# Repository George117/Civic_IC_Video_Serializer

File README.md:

# Civic_IC_Video_Serializer
Civic_IC_Video_Serializer

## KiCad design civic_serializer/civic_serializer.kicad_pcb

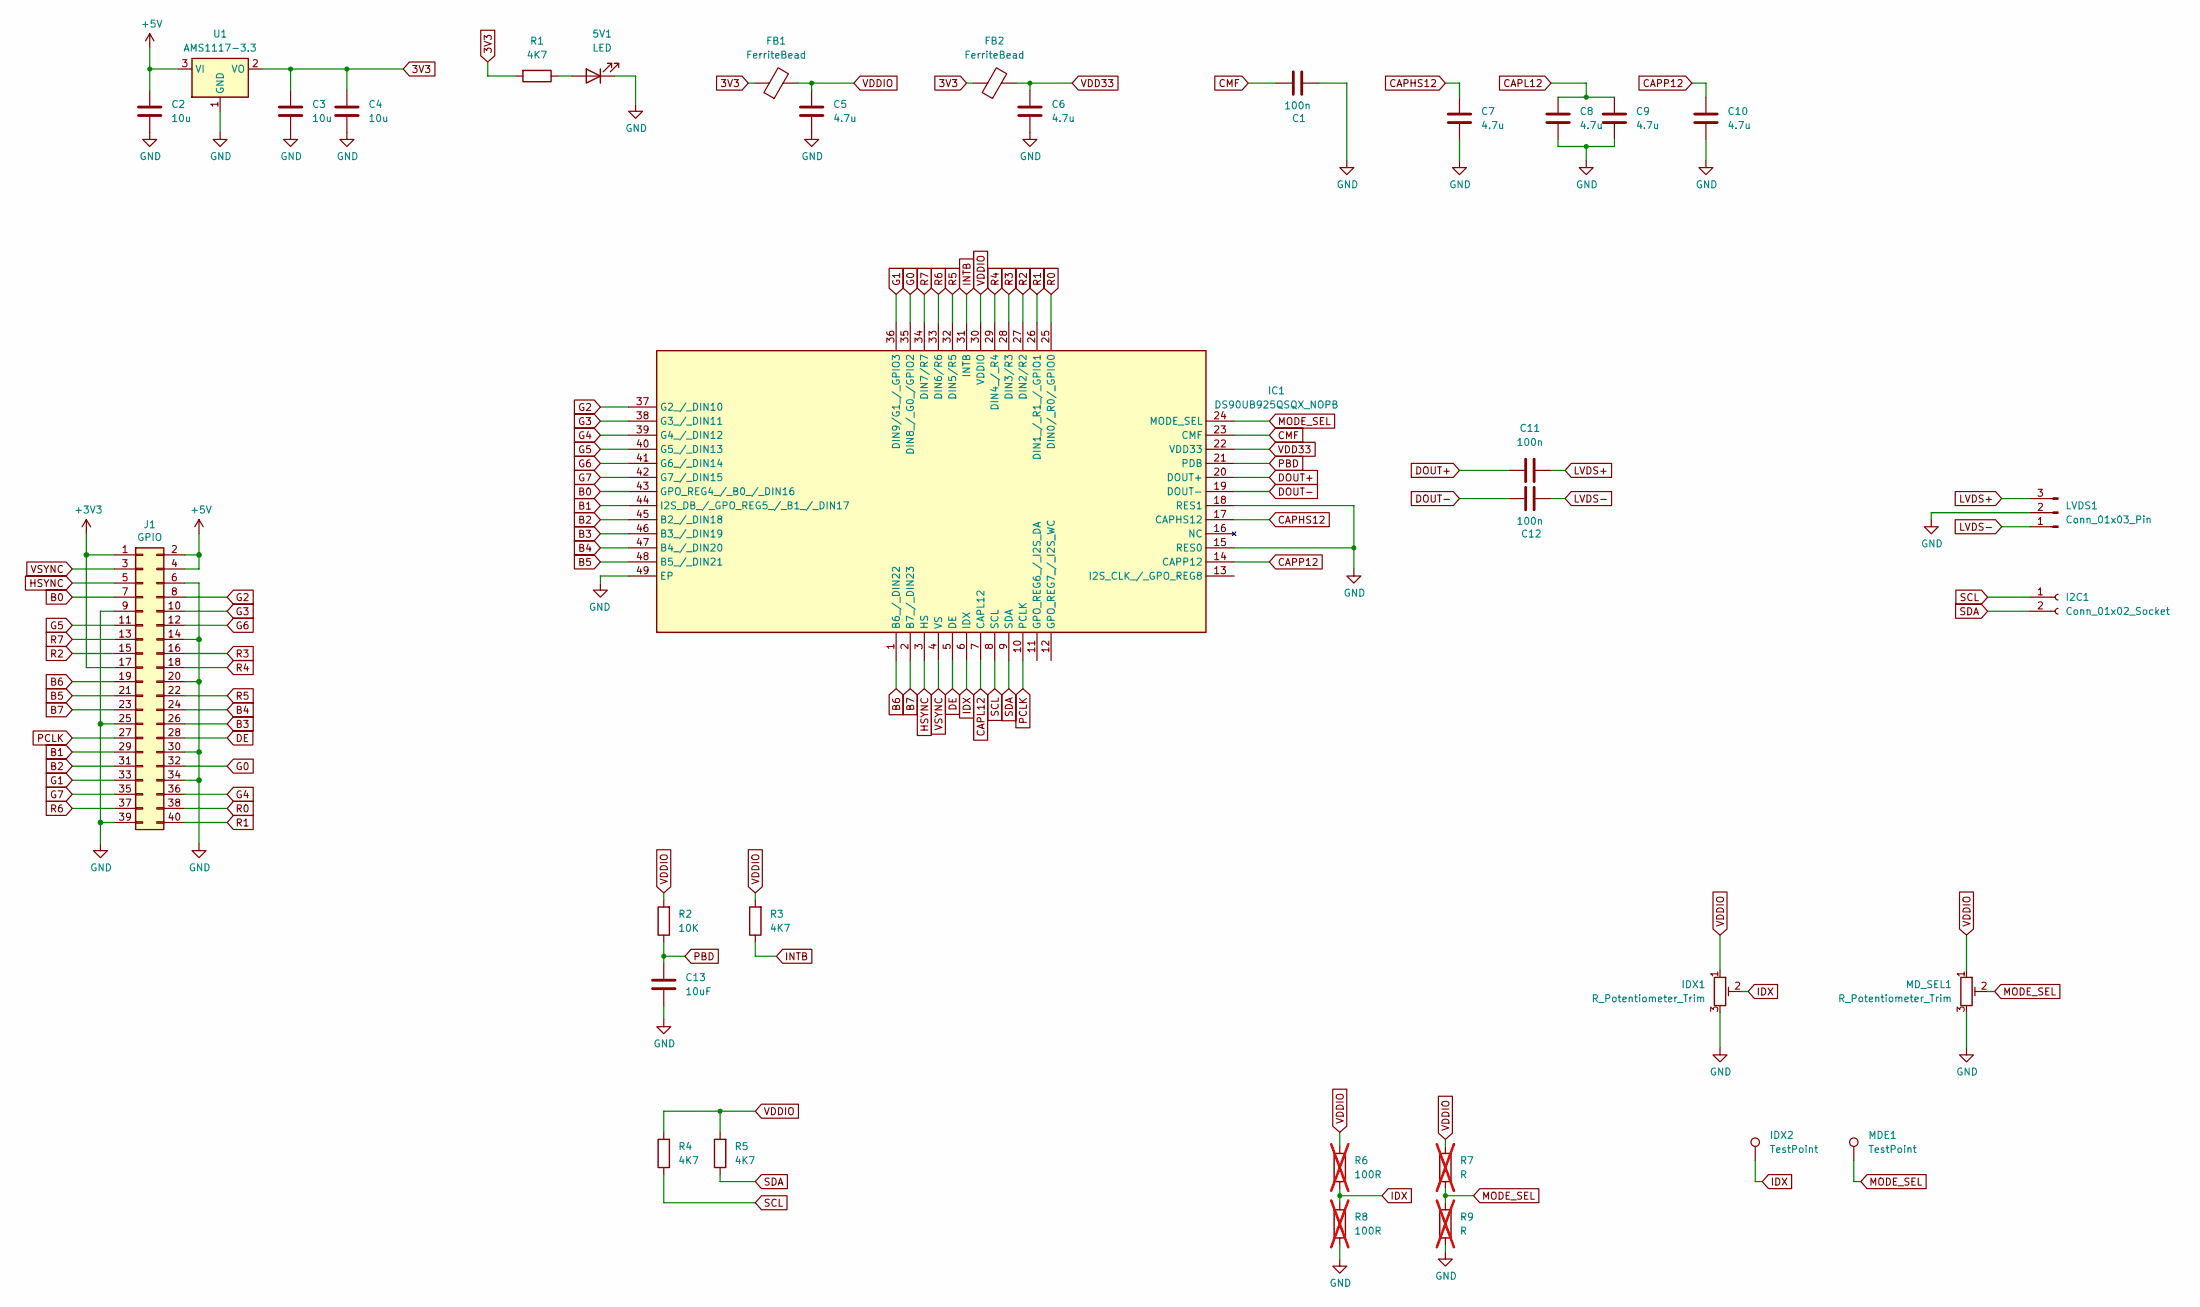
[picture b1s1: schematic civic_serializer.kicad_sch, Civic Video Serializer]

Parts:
5V1: LED; LED_0805_2012Metric_Pad1.15x1.40mm_HandSolder
C1, C11, C12: 100n; C_0603_1608Metric_Pad1.08x0.95mm_HandSolder
C2, C3, C4: 10u; C_0805_2012Metric_Pad1.18x1.45mm_HandSolder
C5, C6, C7, C8, C9, C10: 4.7u; C_0603_1608Metric_Pad1.08x0.95mm_HandSolder
C13: 10uF; C_0603_1608Metric_Pad1.08x0.95mm_HandSolder
FB1, FB2: FerriteBead; L_0603_1608Metric_Pad1.05x0.95mm_HandSolder
I2C1: Conn_01x02_Socket; PinSocket_1x02_P2.54mm_Vertical
IC1: DS90UB925QSQX_NOPB; QFN50P700X700X80-49N-D; Manufacturer_Part_Number DS90UB925QSQX/NOPB; Mouser Part Number 595-DS90UB925QSQXNPB
IDX1: R_Potentiometer_Trim; Potentiometer_Vishay_T93YA_Vertical
IDX2: TestPoint; PinSocket_1x01_P2.54mm_Vertical
J1: GPIO; PinSocket_2x20_P2.54mm_Vertical
LVDS1: Conn_01x03_Pin; JST_NV_B03P-NV_1x03_P5.00mm_Vertical
MDE1: TestPoint; PinSocket_1x01_P2.54mm_Vertical
MD_SEL1: R_Potentiometer_Trim; Potentiometer_Vishay_T93YA_Vertical
R1: 4K7; R_0805_2012Metric_Pad1.20x1.40mm_HandSolder
R2: 10K; R_0603_1608Metric_Pad0.98x0.95mm_HandSolder
R3, R4, R5: 4K7; R_0603_1608Metric_Pad0.98x0.95mm_HandSolder
R6, R8: 100R; R_0603_1608Metric_Pad0.98x0.95mm_HandSolder; not fitted
R7, R9: R; R_0603_1608Metric_Pad0.98x0.95mm_HandSolder; not fitted
U1: AMS1117-3.3; SOT-223-3_TabPin2

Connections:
3V3: C3.1, C4.1, FB1.1, FB2.1, R1.2, U1.2 (VO)
+3V3: J1.1, J1.17
+5V: C2.1, J1.2, J1.4, U1.3 (VI)
B0: IC1.43 (GPO_REG4_/_B0_/_DIN16), J1.7
B1: IC1.44 (I2S_DB_/_GPO_REG5_/_B1_/_DIN17), J1.29
B2: IC1.45 (B2_/_DIN18), J1.31
B3: IC1.46 (B3_/_DIN19), J1.26
B4: IC1.47 (B4_/_DIN20), J1.24
B5: IC1.48 (B5_/_DIN21), J1.21
B6: IC1.1 (B6_/_DIN22), J1.19
B7: IC1.2 (B7_/_DIN23), J1.23
CAPHS12: C7.1, IC1.17 (CAPHS12)
CAPL12: C8.1, C9.1, IC1.7 (CAPL12)
CAPP12: C10.1, IC1.14 (CAPP12)
CMF: C1.1, IC1.23 (CMF)
DE: IC1.5 (DE), J1.28
DOUT+: C11.1, IC1.20 (DOUT+)
DOUT-: C12.1, IC1.19 (DOUT-)
G0: IC1.35 (DIN8_/_G0_/GPIO2), J1.32
G1: IC1.36 (DIN9/G1_/_GPIO3), J1.33
G2: IC1.37 (G2_/_DIN10), J1.8
G3: IC1.38 (G3_/_DIN11), J1.10
G4: IC1.39 (G4_/_DIN12), J1.36
G5: IC1.40 (G5_/_DIN13), J1.11
G6: IC1.41 (G6_/_DIN14), J1.12
G7: IC1.42 (G7_/_DIN15), J1.35
GND: 5V1.1 (K), C1.2, C2.2, C3.2, C4.2, C5.2, C6.2, C7.2, C8.2, C9.2, C10.2, C13.2, IC1.15 (RES0), IC1.18 (RES1), IC1.49 (EP), IDX1.3, J1.6, J1.9, J1.14, J1.20, J1.25, J1.30, J1.34, J1.39, LVDS1.2, MD_SEL1.3, R8.1, R9.1, U1.1 (GND)
HSYNC: IC1.3 (HS), J1.5
IDX: IC1.6 (IDX), IDX1.2, IDX2.1, R6.1, R8.2
INTB: IC1.31 (INTB), R3.1
LVDS+: C11.2, LVDS1.3
LVDS-: C12.2, LVDS1.1
MODE_SEL: IC1.24 (MODE_SEL), MDE1.1, MD_SEL1.2, R7.1, R9.2
unnamed: 5V1.2 (A), R1.1
PBD: C13.1, IC1.21 (PDB), R2.1
PCLK: IC1.10 (PCLK), J1.27
R0: IC1.25 (DIN0/_R0/_GPIO0), J1.38
R1: IC1.26 (DIN1_/_R1_/_GPIO1), J1.40
R2: IC1.27 (DIN2/R2), J1.15
R3: IC1.28 (DIN3/R3), J1.16
R4: IC1.29 (DIN4_/_R4), J1.18
R5: IC1.32 (DIN5/R5), J1.22
R6: IC1.33 (DIN6/R6), J1.37
R7: IC1.34 (DIN7/R7), J1.13
SCL: I2C1.1, IC1.8 (SCL), R4.1
SDA: I2C1.2, IC1.9 (SDA), R5.1
VDD33: C6.1, FB2.2, IC1.22 (VDD33)
VDDIO: C5.1, FB1.2, IC1.30 (VDDIO), IDX1.1, MD_SEL1.1, R2.2, R3.2, R4.2, R5.2, R6.2, R7.2
VSYNC: IC1.4 (VS), J1.3

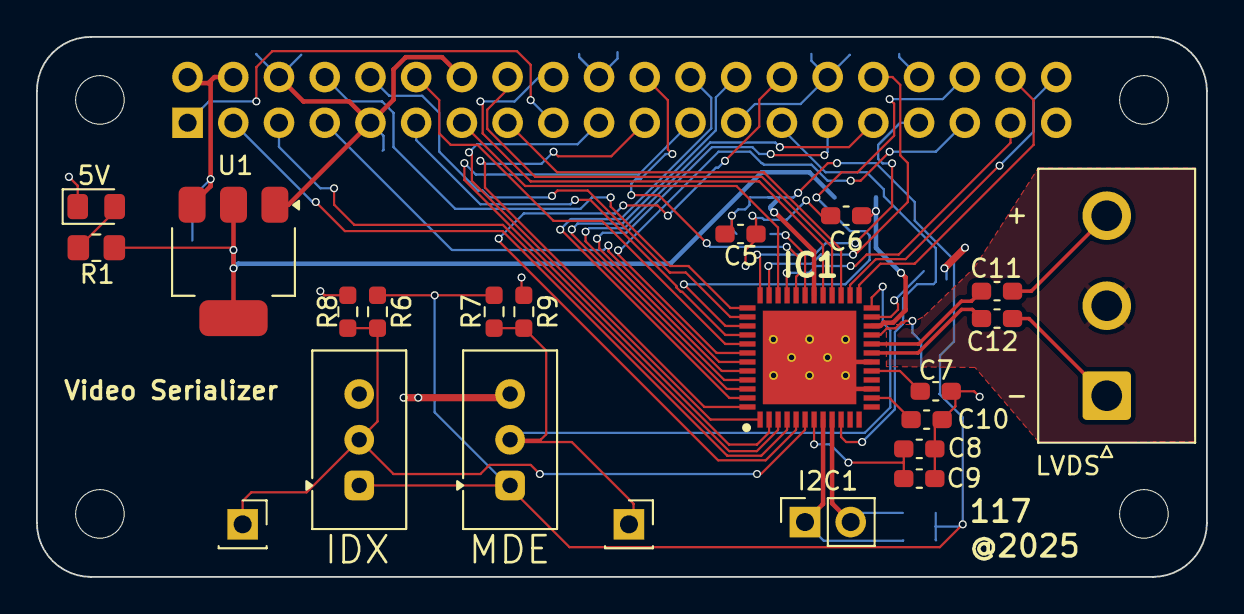
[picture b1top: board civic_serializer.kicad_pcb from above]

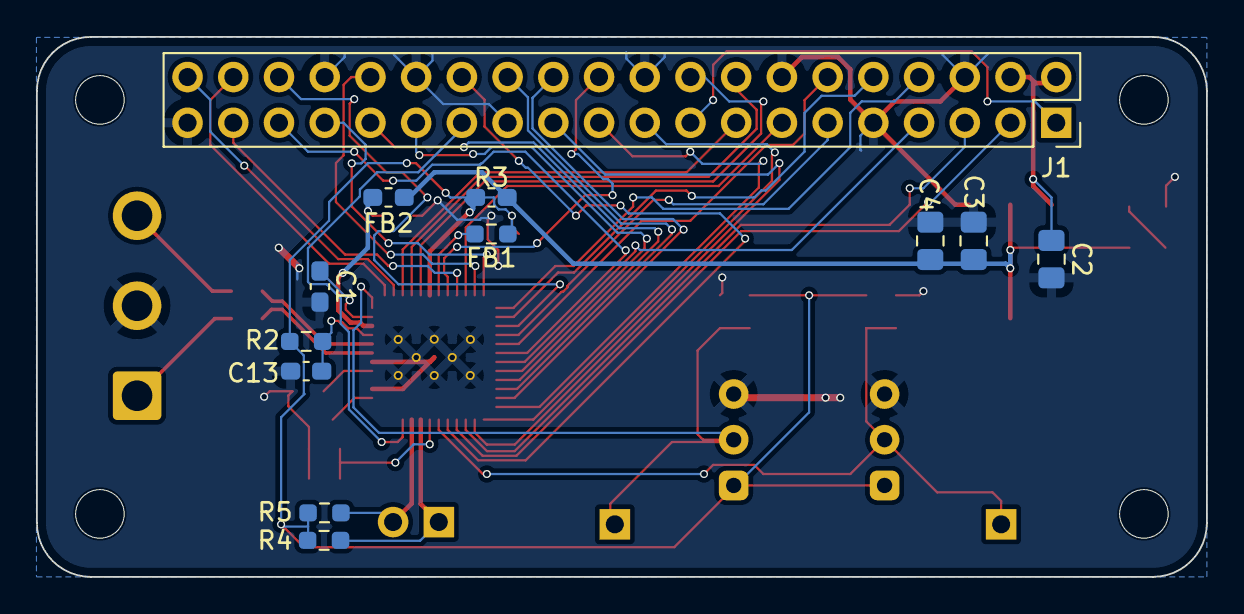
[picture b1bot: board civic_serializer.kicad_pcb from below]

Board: 2 copper layers, 65.0 x 30.0 mm, 38 parts (12 on the bottom side), 49 nets.

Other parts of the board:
MH1, MH2, MH3, MH4: MountingHole_2.7mm_M2.5

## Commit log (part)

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2025-02-10 - added documentation
2025-02-10 - added pcb folder
2025-02-11 - added initial template - added serializer sym/footprint - updated connection labels at rpi connector
2025-02-11 - routed part of schematic
2025-02-11 - finished part of the schematic
2025-02-12 - added ev board docu
2025-02-12 - added rpi documentation
2025-02-12 - schematic finished
2025-02-12 - done some of the layout
2025-02-13 - layout finished
2025-02-13 - fixed drc error
2025-02-13 - updated gerber settings to comply with jlcpcb
2025-02-13 - minor lvds trace lenght matching - added generated gerber files
2025-02-13 - updated vias dimensions - regenerated gerbers
